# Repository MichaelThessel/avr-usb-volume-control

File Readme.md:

### USB Volume Control ###

Firmware for USB volume control board

This is project utilizes the [VUSB library](https://github.com/MichaelThessel/avr-usb-volume-control) by Objective Development. A detailed description of the project can be found [here](http://michaelthessel.com/usb-volume-control/). The KiCad design files are located in the PCB folder.

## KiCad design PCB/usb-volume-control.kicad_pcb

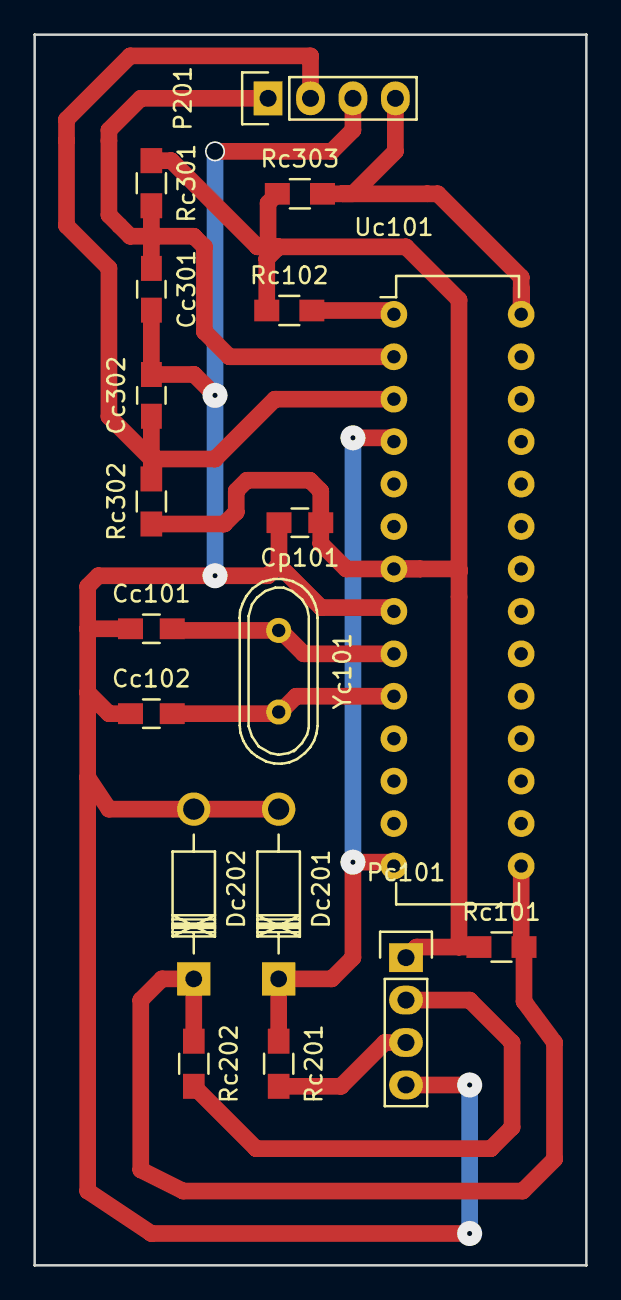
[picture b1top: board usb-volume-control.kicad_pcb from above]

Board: 2 copper layers, 33.0 x 73.7 mm, 18 parts (0 on the bottom side), 12 nets.

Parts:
Cc101, Cc102: 22pF; C_0805_HandSoldering
Cc301, Cc302: 1uF; C_0805_HandSoldering
Cp101: 10uF; C_0805_HandSoldering
Dc201, Dc202: 3V6; Diode_DO-41_SOD81_Horizontal_RM10
P201: ROT ENC; Pin_Header_Straight_1x04
Pc101: USB; Pin_Header_Straight_1x04
Rc101, Rc102, Rc301, Rc302, Rc303: 2k; R_0805_HandSoldering
Rc201, Rc202: 47R; R_0805_HandSoldering
Uc101: ATMEGA328P-P; DIP-28_W7.62mm
Yc101: Crystal; Crystal_HC49-U_Vertical

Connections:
GND: Cc101.1, Cc102.1, Cc301.2, Cc302.2, Cp101.2, Dc201.2, Dc202.2, P201.3, Pc101.4, Uc101.8
unnamed: Cc101.2, Uc101.9, Yc101.1
unnamed: Cc102.2, Uc101.10, Yc101.2
unnamed: Cc301.1, P201.1, Rc301.2, Uc101.2
unnamed: Cc302.1, P201.2, Rc302.2, Uc101.3
unnamed: Dc201.1, Rc201.1, Uc101.4, Uc101.14
unnamed: Dc202.1, Rc101.2, Rc202.1, Uc101.15
unnamed: P201.4, Rc303.2, Uc101.28
unnamed: Pc101.2, Rc202.2
unnamed: Pc101.3, Rc201.2
unnamed: Rc102.2, Uc101.1
VCC: Cp101.1, Pc101.1, Rc101.1, Rc102.1, Rc301.1, Rc302.1, Rc303.1, Uc101.7

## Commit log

2016-04-19 Removed keycodes
2016-04-20 Added PCB layout
2016-04-21 Improved PCB layout
2016-04-30 Fixed connection error
2016-05-02 Changed rotary encoder capacitor value
2016-05-02 Added support for rotary encoder push button
2016-05-03 Improved debounce
2016-05-03 Switched to timers for debouncing
2016-05-04 Added Makefile
